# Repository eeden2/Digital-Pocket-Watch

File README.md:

# Digital-Pocket-Watch
This is my first invention which implements functionality for time, obviously, and a connection to a remote camera server.

# 3D-View

The parts are all in the mainv2/Footprints. A list here will be provided later.
- __UPDATE (10/01/2023)__
  
      The Firmware currently supports all fudamental rpotocols (I2C, WIFI, SPI, etc.)
      It also has the UI implemented for basic functionality,. Server setup for camera
      display is the only part left, but the lack of ability to manufacture it from costs
      could leave this project as is, finished.
- __The Drivers for the display are a GC9A01 SPI and a CST816S I2C Touch Interface__

# PCB

# Schematic

# UI Interface

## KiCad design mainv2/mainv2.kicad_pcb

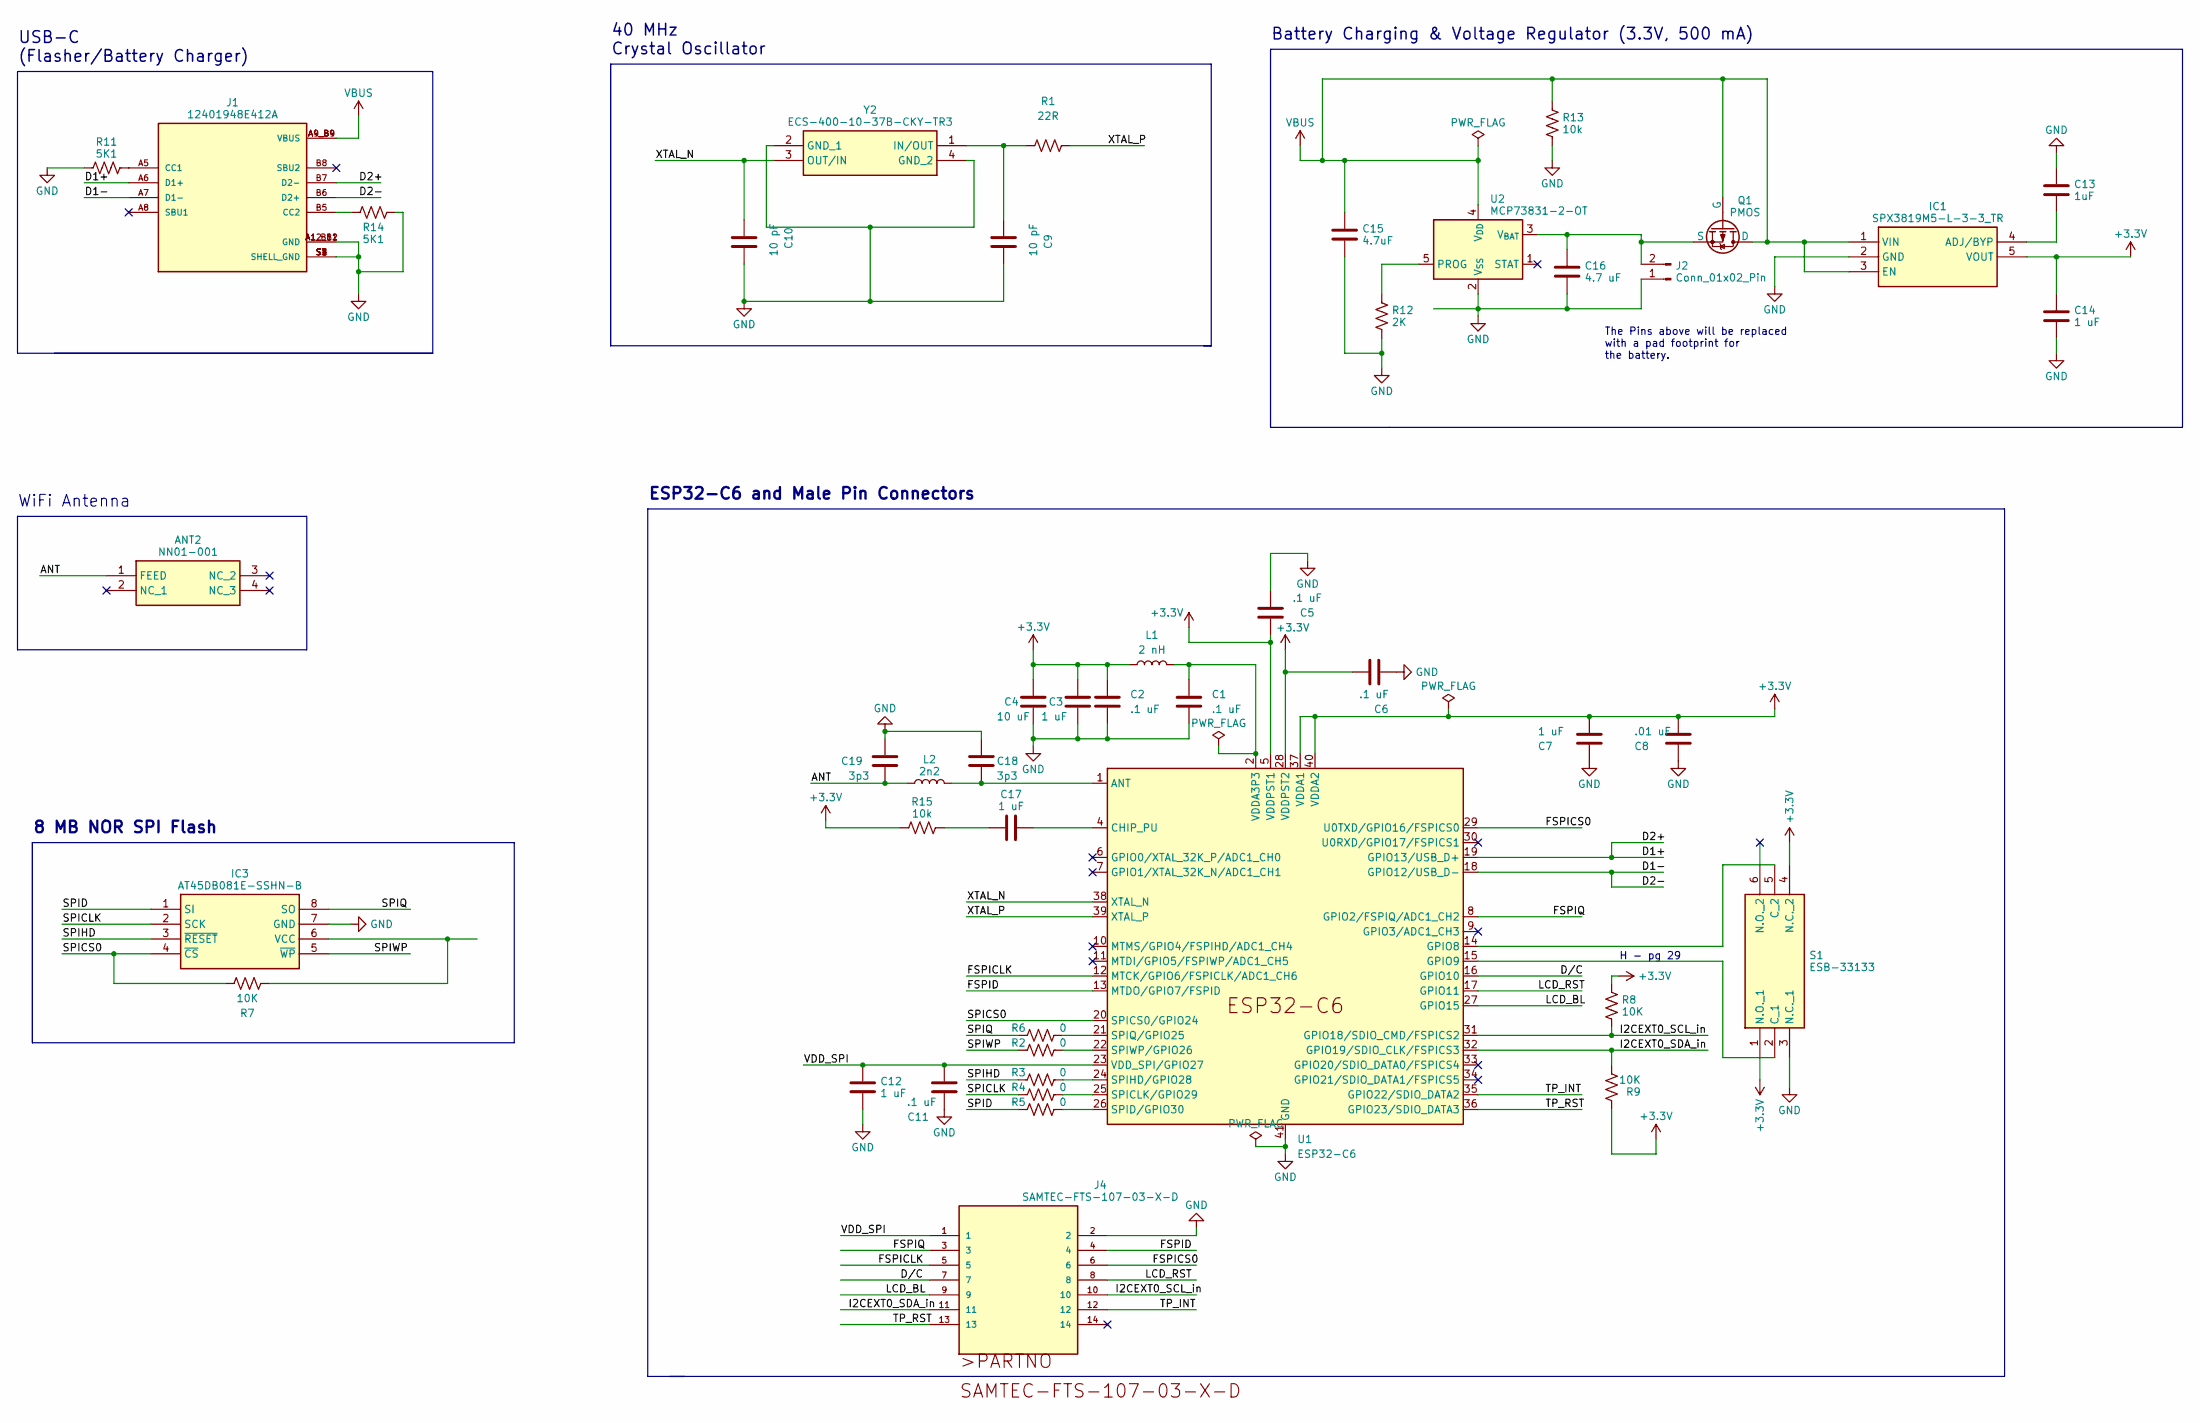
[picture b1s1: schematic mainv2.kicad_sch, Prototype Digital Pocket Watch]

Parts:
ANT2: NN01-001; NN01001; Manufacturer_Part_Number NN01-001
C1, C2, C5, C6, C11: .1 uF; CAPC0603X33N
C3, C7, C12, C14, C17: 1 uF; CAPC0603X35N
C4: 10 uF; CAPC1608X90N
C8: .01 uF; CAPC0603X33N
C9, C10: 10 pF; C0603
C13: 1uF; CAPC0603X35N
C15: 4.7uF; CAPC1005X55N
C16: 4.7 uF; CAPC1005X55N
C18, C19: 3p3; CAPC1005X55N
IC1: SPX3819M5-L-3-3_TR; SOT95P280X145-5N; Mouser Part Number 701-SPX3819M5-L-33TR
IC3: AT45DB081E-SSHN-B; SOIC127P600X175-8N; Mouser Part Number 988-AT45DB081ESSHN-B
J1: 12401948E412A; AMPHENOL_12401948E412A; PARTREV 3
J2: Conn_01x02_Pin; PinHeader_1x02_P2.54mm_Vertical
J4: SAMTEC-FTS-107-03-X-D
L1: 2 nH; MLG0603
L2: 2n2; INDC2012X103N
Q1: PMOS; IRFR9210PBFBE3
R1: 22R; RESC6332X65N
R2, R3, R4, R5, R6: 0; RESC1608X55N
R7, R8, R9: 10K; RESC3116X65N
R11, R14: 5K1; RESC6432X65N
R12: 2K; RESC1608X55N
R13, R15: 10k; RESC3116X65N
S1: ESB-33133; ESB33133; Mouser Part Number 667-ESB-33133
U1: ESP32-C6; QFN-40-1EP_5x5mm_P0.4mm_EP3.6x3.6mm
U2: MCP73831-2-OT; SOT-23-5
Y2: ECS-400-10-37B-CKY-TR3; ECS4001037BCKYTR3; Mouser Part Number 520-EC4001037BCKYTR3

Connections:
+3.3V: C2.1, C3.1, C4.1, C5.1, C6.1, C7.1, C8.1, C14.1, IC1.5 (VOUT), L1.1, R8.1, R9.1, R15.1, S1.1 (N.O._1), S1.4 (N.C._2), U1.5 (VDDPST1), U1.28 (VDDPST2), U1.37 (VDDA1), U1.40 (VDDA2)
/ANT: ANT2.1 (FEED), C19.2, L2.1
/D1+: J1.A6 (D1+), J1.B7 (D2-), U1.19 (GPIO13/USB_D+)
/D1-: J1.A7 (D1-), J1.B6 (D2+), U1.18 (GPIO12/USB_D-)
/D/C: J4.7, U1.16 (GPIO10)
/FSPICLK: J4.5, U1.12 (MTCK/GPIO6/FSPICLK/ADC1_CH6)
/FSPICS0: J4.6, U1.29 (U0TXD/GPIO16/FSPICS0)
/FSPID: J4.4, U1.13 (MTDO/GPIO7/FSPID)
/FSPIQ: J4.3, U1.8 (GPIO2/FSPIQ/ADC1_CH2)
/I2CEXT0_SCL_in: J4.10, R8.2, U1.31 (GPIO18/SDIO_CMD/FSPICS2)
/I2CEXT0_SDA_in: J4.11, R9.2, U1.32 (GPIO19/SDIO_CLK/FSPICS3)
/LCD_BL: J4.9, U1.27 (GPIO15)
/LCD_RST: J4.8, U1.17 (GPIO11)
/SPICLK: IC3.2 (SCK), R4.1
/SPICS0: IC3.4 (~CS), R7.1, U1.20 (SPICS0/GPIO24)
/SPID: IC3.1 (SI), R5.1
/SPIHD: IC3.3 (~RESET), R3.1
/SPIQ: IC3.8 (SO), R6.1
/SPIWP: IC3.5 (~WP), R2.1
/TP_INT: J4.12, U1.35 (GPIO22/SDIO_DATA2)
/TP_RST: J4.13, U1.36 (GPIO23/SDIO_DATA3)
/VDD_SPI: C11.2, C12.2, J4.1, U1.23 (VDD_SPI/GPIO27)
/XTAL_N: C10.1, U1.38 (XTAL_N), Y2.3 (OUT/IN)
/XTAL_P: R1.2, U1.39 (XTAL_P)
GND: C1.2, C2.2, C3.2, C4.2, C5.2, C6.2, C7.2, C8.2, C9.2, C10.2, C11.1, C12.1, C13.1, C14.2, C15.2, C16.2, C18.1, C19.1, IC1.2 (GND), IC3.7 (GND), J1.A1_B12 (GND), J1.A12_B1 (GND), J1.S1 (SHELL_GND), J1.S2 (SHELL_GND), J1.S3 (SHELL_GND), J1.S4 (SHELL_GND), J2.1, J4.2, R11.1, R12.2, R13.2, R14.2, S1.3 (N.C._1), U1.41 (GND), U2.2 (V_{SS}), Y2.2 (GND_1), Y2.4 (GND_2)
unnamed: C1.1, L1.2, U1.2 (VDDA3P3), U1.3 (VDDA3P3)
unnamed: C17.1, R15.2
unnamed: C13.2, IC1.4 (ADJ/BYP)
unnamed: IC3.6 (VCC), R7.2
unnamed: J1.A5 (CC1), R11.2
unnamed: J1.B5 (CC2), R14.1
unnamed: C16.1, J2.2, Q1.3 (S), U2.3 (V_{BAT})
unnamed: S1.2 (C_1), U1.15 (GPIO9)
unnamed: S1.5 (C_2), U1.14 (GPIO8)
unnamed: C18.2, L2.2, U1.1 (ANT)
unnamed: C17.2, U1.4 (CHIP_PU)
unnamed: R4.2, U1.25 (SPICLK/GPIO29)
unnamed: R5.2, U1.26 (SPID/GPIO30)
unnamed: R3.2, U1.24 (SPIHD/GPIO28)
unnamed: R6.2, U1.21 (SPIQ/GPIO25)
unnamed: R2.2, U1.22 (SPIWP/GPIO26)
unnamed: R12.1, U2.5 (PROG)
unnamed: C9.1, R1.1, Y2.1 (IN/OUT)
VBUS: C15.1, IC1.1 (VIN), IC1.3 (EN), J1.A4_B9 (VBUS), J1.A9_B4 (VBUS), Q1.1 (D), Q1.2 (G), R13.1, U2.4 (V_{DD})

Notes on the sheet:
H - pg 29
ESP32-C6 and Male Pin Connectors
The Pins above will be replaced with a pad footprint for the battery.
USB-C (Flasher/Battery Charger)
Battery Charging & Voltage Regulator (3.3V, 500 mA)
WiFi Antenna
8 MB NOR SPI Flash
40 MHz Crystal Oscillator

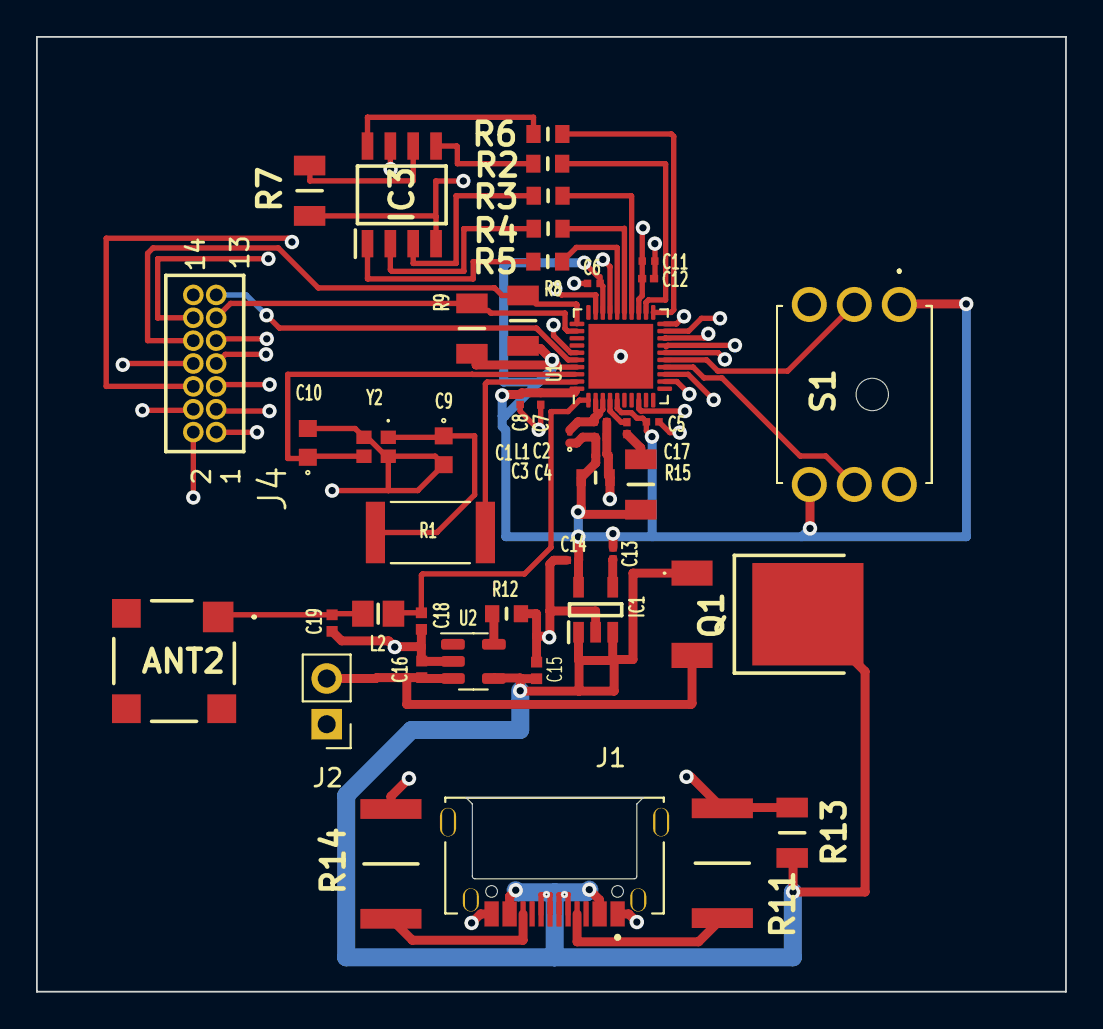
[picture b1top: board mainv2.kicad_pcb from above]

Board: 4 copper layers, 57.2 x 53.0 mm, 46 parts (0 on the bottom side), 44 nets.

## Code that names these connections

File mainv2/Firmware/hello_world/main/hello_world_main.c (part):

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

// 4MB Flash SPI
#define SPICLK 25
#define SPID 26
#define SPIQ 21
#define SPICS0 20

// LCD SPI Pins
#define FSPI_CLK GPIO_NUM_6
#define FSPID GPIO_NUM_7
#define FSPIQ GPIO_NUM_2
#define FSPICS0 GPIO_NUM_16
#define LCD_RST GPIO_NUM_15
#define LCD_BL GPIO_NUM_11
#define D_C GPIO_NUM_10

//LCD Properties
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
// I2C Touch Panel
#define I2XEXT0_SCL_in GPIO_NUM_18
#define I2CEXT0_SDA_in GPIO_NUM_19
#define TP_INT GPIO_NUM_22
#define TP_RST GPIO_NUM_23

//Antenna
#define ANT 1

//USB Diffs
#define D_PLUS GPIO_NUM_13
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    gpio_config_t bk_gpio_config = 
    {
        .mode = GPIO_MODE_OUTPUT,
        .pin_bit_mask = 1ULL << LCD_BL
    };
 
    //Setting GPIO pins to alternate fucntions via the GPIO Matrix
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    esp_lcd_panel_io_spi_config_t config_IO = 
    {
        .dc_gpio_num = D_C,
        .cs_gpio_num = FSPICS0,
        .pclk_hz = LCD_PIXEL_CLOCK_HZ,
        .lcd_cmd_bits = LCD_CMD_BITS,
        .lcd_param_bits = LCD_PARAM_BITS,
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    esp_lcd_panel_handle_t handle_my_panel = NULL;
    esp_lcd_panel_dev_config_t config_my_panel = 
    {
        .reset_gpio_num = LCD_RST,
        .rgb_endian = LCD_RGB_ENDIAN_BGR,
        .bits_per_pixel = 16,
    };
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
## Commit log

2023-08-03 Added a setup for the LCD SPI Bus.
2023-08-03 Tidying up
2023-08-06 added a .gitignore
2023-08-06 updated layout 8/06/2023
2023-08-06 Redesigned board and setup LCD Display Driver.
2023-08-06 cleanup
2023-08-07 Added Current Screenshots for a Visual Flair.
2023-08-07 Board Update
2023-08-07 laptop check
2023-08-27 Restructed project with no include errors
2023-09-03 Setup the WIFI driver and implemented watch UI.

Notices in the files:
mainv2/Firmware/hello_world/main/hello_world_main.c:
SPDX-FileCopyrightText: 2010-2022 Espressif Systems (Shanghai) CO LTD
SPDX-License-Identifier: CC0-1.0
